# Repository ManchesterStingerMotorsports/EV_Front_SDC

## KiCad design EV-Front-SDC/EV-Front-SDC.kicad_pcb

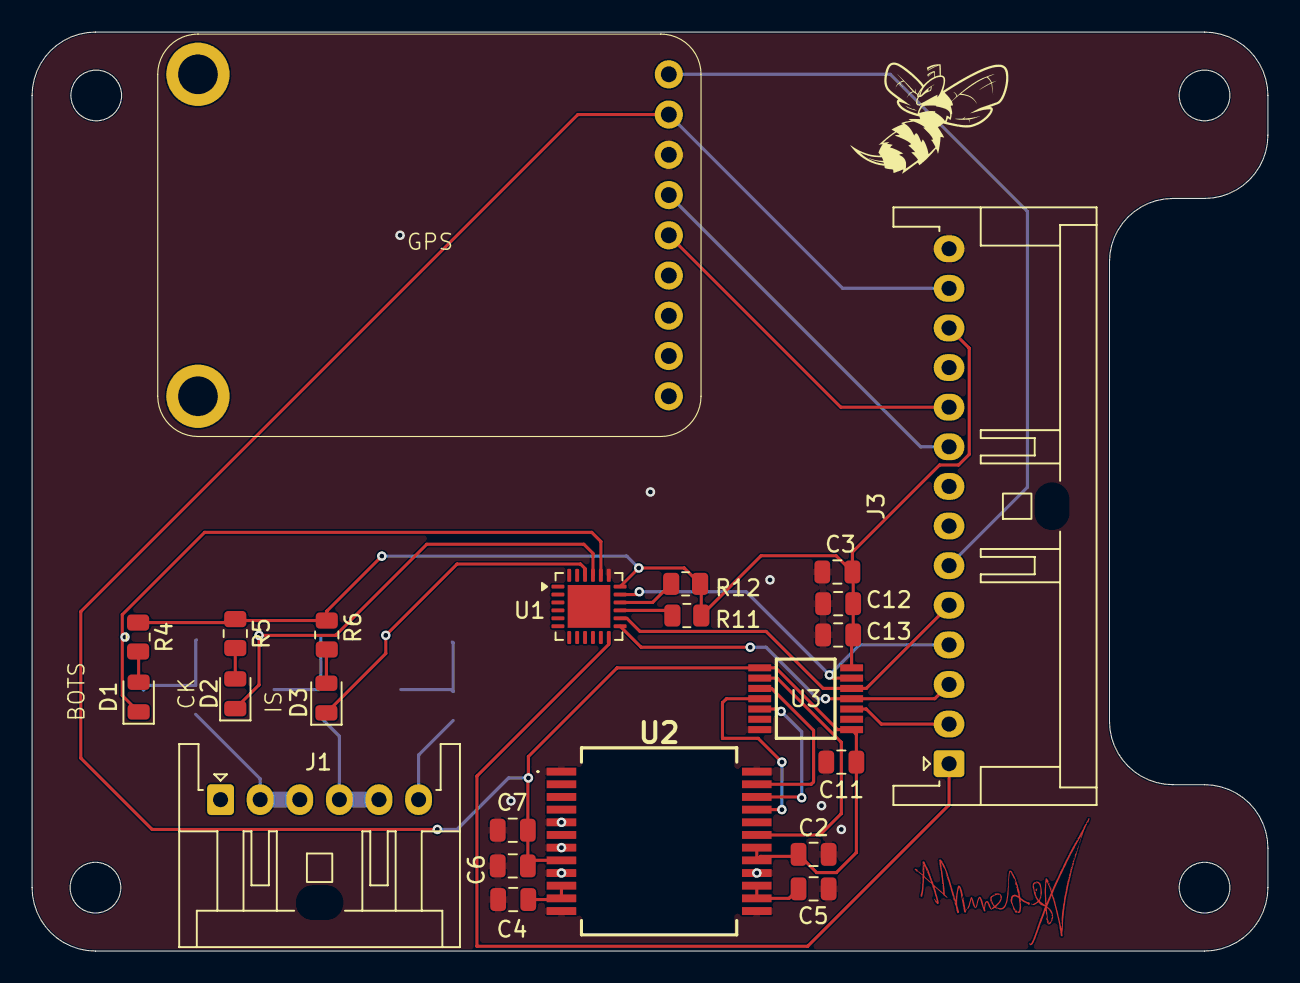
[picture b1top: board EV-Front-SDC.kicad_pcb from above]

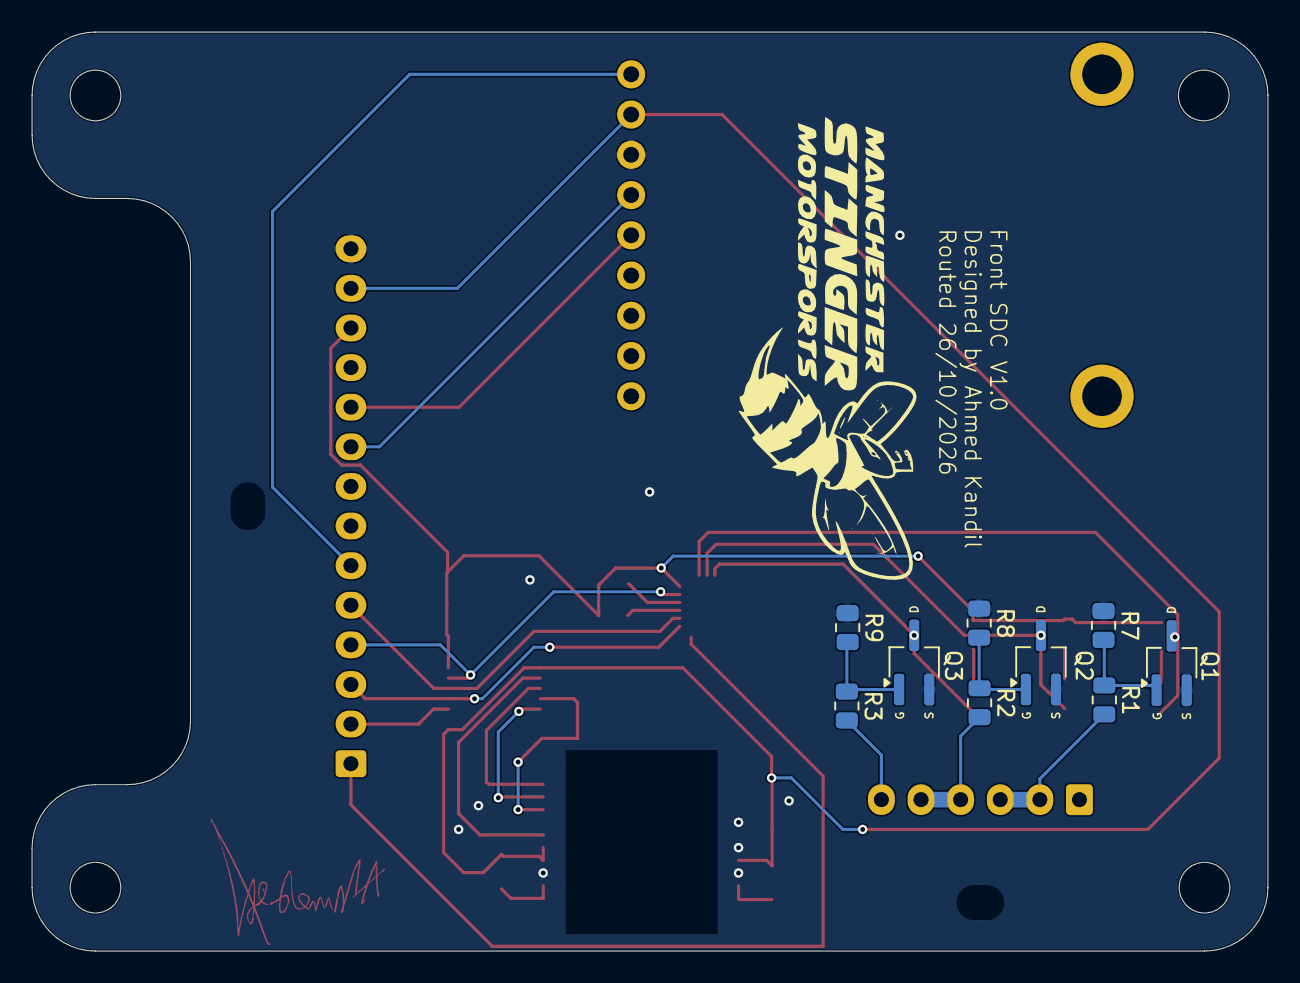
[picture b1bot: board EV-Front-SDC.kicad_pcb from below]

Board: 2 copper layers, 78.0 x 58.0 mm, 32 parts (9 on the bottom side), 31 nets.

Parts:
C2, C3, C7, C11, C12: 0.1u; C_0805_2012Metric
C4: 10u; C_0805_2012Metric
C5, C6, C13: 1u; C_0805_2012Metric
D1, D2, D3: LED; LED_0805_2012Metric
J1: Conn_01x06; JST_XA_S06B-XASK-1_1x06_P2.50mm_Horizontal
J2: GPS
J3: Conn_01x14; JST_XA_S14B-XASK-1_1x14_P2.50mm_Horizontal
Q1, Q2, Q3: BSS205N; MOSFET_Single_SOT-23
R1, R2, R3: 75K; R_0805_2012Metric
R4, R5, R6: 300R; R_0805_2012Metric
R7, R8, R9: 25k; R_0805_2012Metric
R11, R12: 10k; R_0805_2012Metric
U1: QFN-24-1EP_4x4mm_P0.5mm_EP2.7x2.7mm
U2: SCH16T-K01-10; SCH16TK0110
U3: MAX3390EEUD_T; SOP65P640X110-14N

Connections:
5V_CS_C: J3.1, U1.12 (CS)
5V_CS_D: J3.2, U3.10 (O_VCC4)
5V_MISO: J3.4, U1.17 (SDO), U3.13 (I_VCC1)
5V_MOSI: J3.5, U1.14 (SDI), U3.12 (O_VCC2)
5V_SCLK: J3.3, U1.13 (SCLK), U3.11 (O_VCC3)
+3V3: C2.1, C6.1, C7.1, C11.1, J2.2, J3.13, U2.8 (V3P3_1), U2.17 (V3P3_2), U2.18 (VDDIO), U3.1 (VL), U3.8 (~THREE-STATE)
+5V: C3.1, C12.1, C13.1, J3.12, R4.1, R5.1, R6.1, R11.2, R12.2, U1.18 (VCC), U3.14 (VCC)
BOTS: J1.2, J1.3, R1.2
BOTS_S: D1.1 (K), Q1.3 (D), U1.20 (P0.0)
CK_S: D2.1 (K), Q2.3 (D), U1.21 (P0.1)
CS_D: U2.22 (CS), U3.5 (I_VL4)
Cockpit: J1.4, J1.5, R2.2
GND: C2.2, C3.2, C4.2, C5.2, C6.2, C7.2, C11.2, C12.2, C13.2, J2.3, J3.14, Q1.2 (S), Q2.2 (S), Q3.2 (S), R7.1, R8.1, R9.1, U1.19 (GND), U2.1 (HEATSINK_1), U2.5 (RESERVED_1), U2.7 (RESERVED_2), U2.9 (GND_1), U2.12 (GND_2), U2.13 (GND_3), U2.16 (GND_4), U2.24 (HEATSINK_2), U3.7 (GND)
IS_S: D3.1 (K), Q3.3 (D), U1.22 (P0.2)
Inertia Switch: J1.6, R3.2
MISO: U2.19 (MISO), U3.2 (O_VL1)
MOSI: U2.23 (MOSI), U3.3 (I_VL2)
unnamed: D1.2 (A), R4.2
unnamed: D2.2 (A), R5.2
unnamed: D3.2 (A), R6.2
unnamed: Q1.1 (G), R1.1, R7.2
unnamed: Q2.1 (G), R2.1, R8.2
unnamed: Q3.1 (G), R3.1, R9.2
unnamed: R12.1, U1.16 (INT)
unnamed: R11.1, U1.15 (RESET)
unnamed: C4.1, U2.10 (VREGA2), U2.11 (VREGA)
unnamed: C5.1, U2.14 (VREGD2), U2.15 (VREGD)
PPS: J2.1, J3.6
RX: J2.4, J3.9
SCLK: U2.21 (SCK), U3.4 (I_VL3)
TX: J2.5, J3.10
